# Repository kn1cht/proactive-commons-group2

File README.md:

# proactive-commons-group2
proactive-commons-group2 project

## Shiftr.io with ESP32
Please refer to [ESP32 + Noodl + MQTTでpub/subを試してみる - Qiita](https://qiita.com/masaya-oguro/items/5def128399bde690d8a7#%E4%BD%BF%E3%81%84%E6%96%B9).

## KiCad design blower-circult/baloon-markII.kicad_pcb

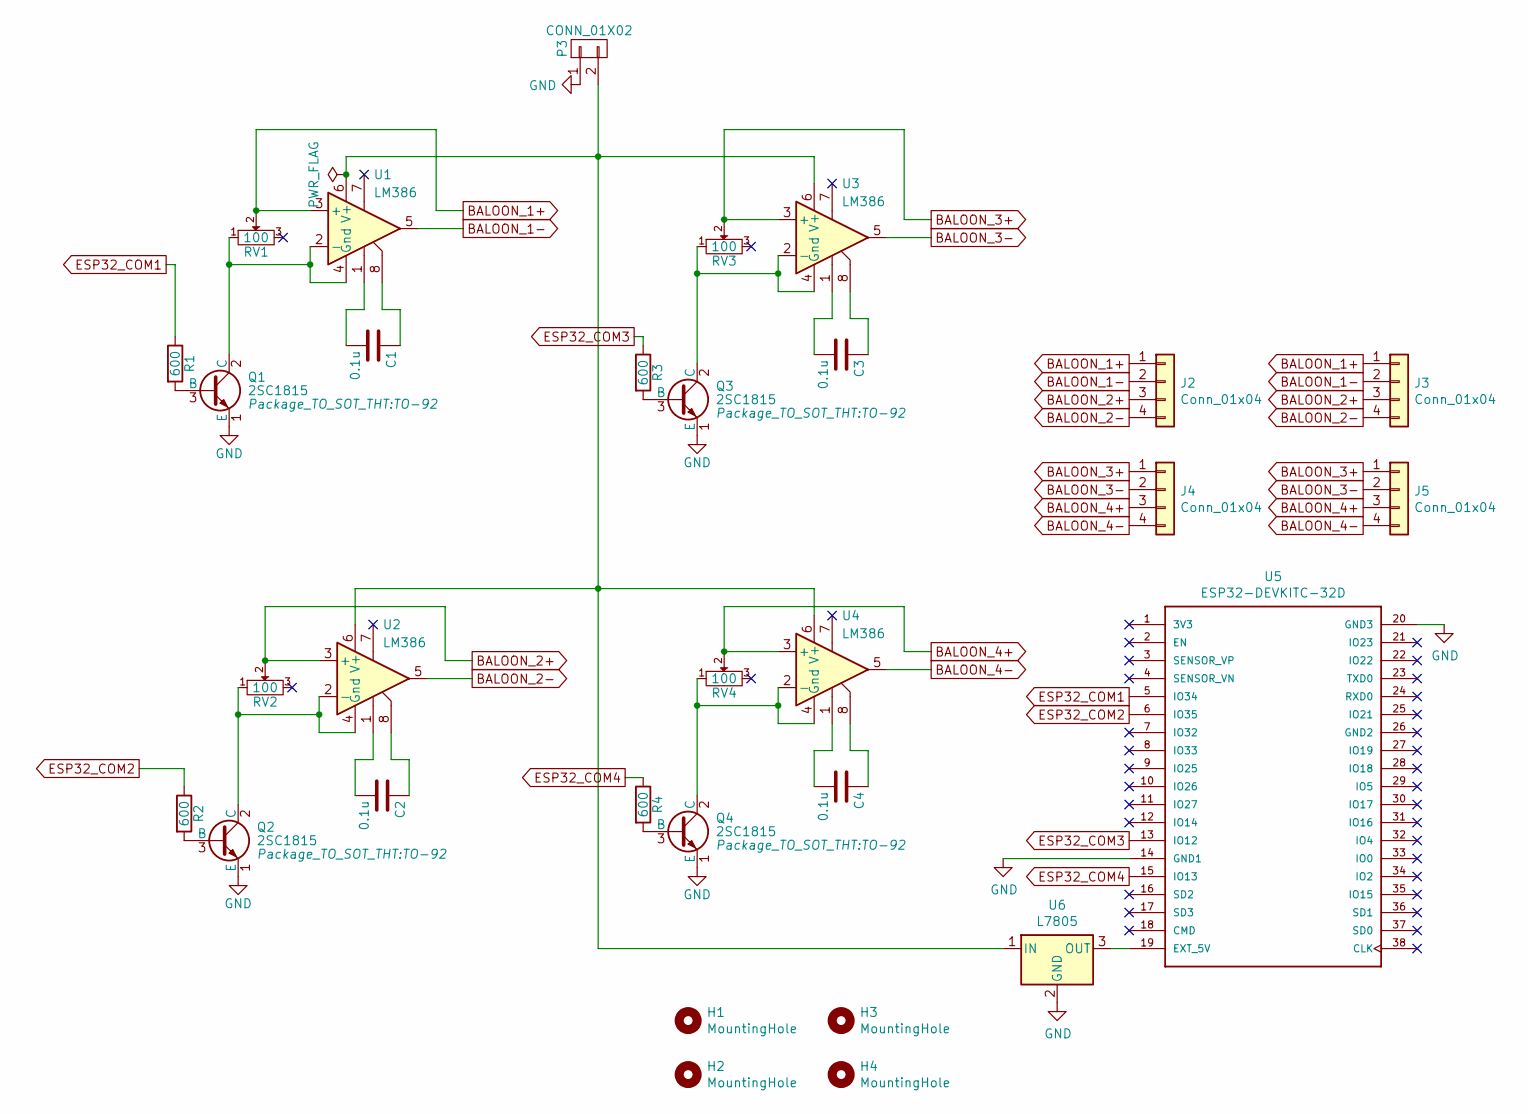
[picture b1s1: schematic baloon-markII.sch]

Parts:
C1, C2, C3, C4: 0.1u; C_Disc_D6.0mm_W2.5mm_P5.00mm
H1, H2, H3, H4: MountingHole; MountingHole_3.2mm_M3
J2, J3, J4, J5: Conn_01x04; Molex_SPOX_5267-04A_1x04_P2.50mm_Vertical
P3: CONN_01X02; Molex_SPOX_5267-02A_1x02_P2.50mm_Vertical
Q1, Q2, Q3, Q4: 2SC1815; TO-92
R1, R2, R3, R4: 600; R_Axial_DIN0204_L3.6mm_D1.6mm_P7.62mm_Horizontal
RV1, RV2, RV3, RV4: 100; Potentiometer_ACP_CA9-H5_Horizontal
U1, U2, U3, U4: LM386; DIP-8_W7.62mm_Socket
U5: ESP32-DEVKITC-32D; MODULE_ESP32-DEVKITC-32D
U6: L7805; TO-220F-3_Horizontal_TabDown

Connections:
BALOON_1+: J2.1, J3.1, RV1.2, U1.3 (+)
BALOON_1-: J2.2, J3.2, U1.5
BALOON_2+: J2.3, J3.3, RV2.2, U2.3 (+)
BALOON_2-: J2.4, J3.4, U2.5
BALOON_3+: J4.1, J5.1, RV3.2, U3.3 (+)
BALOON_3-: J4.2, J5.2, U3.5
BALOON_4+: J4.3, J5.3, RV4.2, U4.3 (+)
BALOON_4-: J4.4, J5.4, U4.5
ESP32_COM1: R1.1, U5.5 (IO34)
ESP32_COM2: R2.1, U5.6 (IO35)
ESP32_COM3: R3.1, U5.13 (IO12)
ESP32_COM4: R4.1, U5.15 (IO13)
GND: P3.1, Q1.1 (E), Q2.1 (E), Q3.1 (E), Q4.1 (E), U5.14 (GND1), U5.20 (GND3), U6.2 (GND)
unnamed: C1.1, U1.8
unnamed: C1.2, U1.1
unnamed: C2.1, U2.8
unnamed: C2.2, U2.1
unnamed: C3.1, U3.8
unnamed: C3.2, U3.1
unnamed: C4.1, U4.8
unnamed: C4.2, U4.1
unnamed: P3.2, U1.6 (V+), U2.6 (V+), U3.6 (V+), U4.6 (V+), U6.1 (IN)
unnamed: Q1.2 (C), RV1.1, U1.2 (-), U1.4 (Gnd)
unnamed: Q1.3 (B), R1.2
unnamed: Q2.2 (C), RV2.1, U2.2 (-), U2.4 (Gnd)
unnamed: Q2.3 (B), R2.2
unnamed: Q3.2 (C), RV3.1, U3.2 (-), U3.4 (Gnd)
unnamed: Q3.3 (B), R3.2
unnamed: Q4.2 (C), RV4.1, U4.2 (-), U4.4 (Gnd)
unnamed: Q4.3 (B), R4.2
unnamed: U5.19 (EXT_5V), U6.3 (OUT)

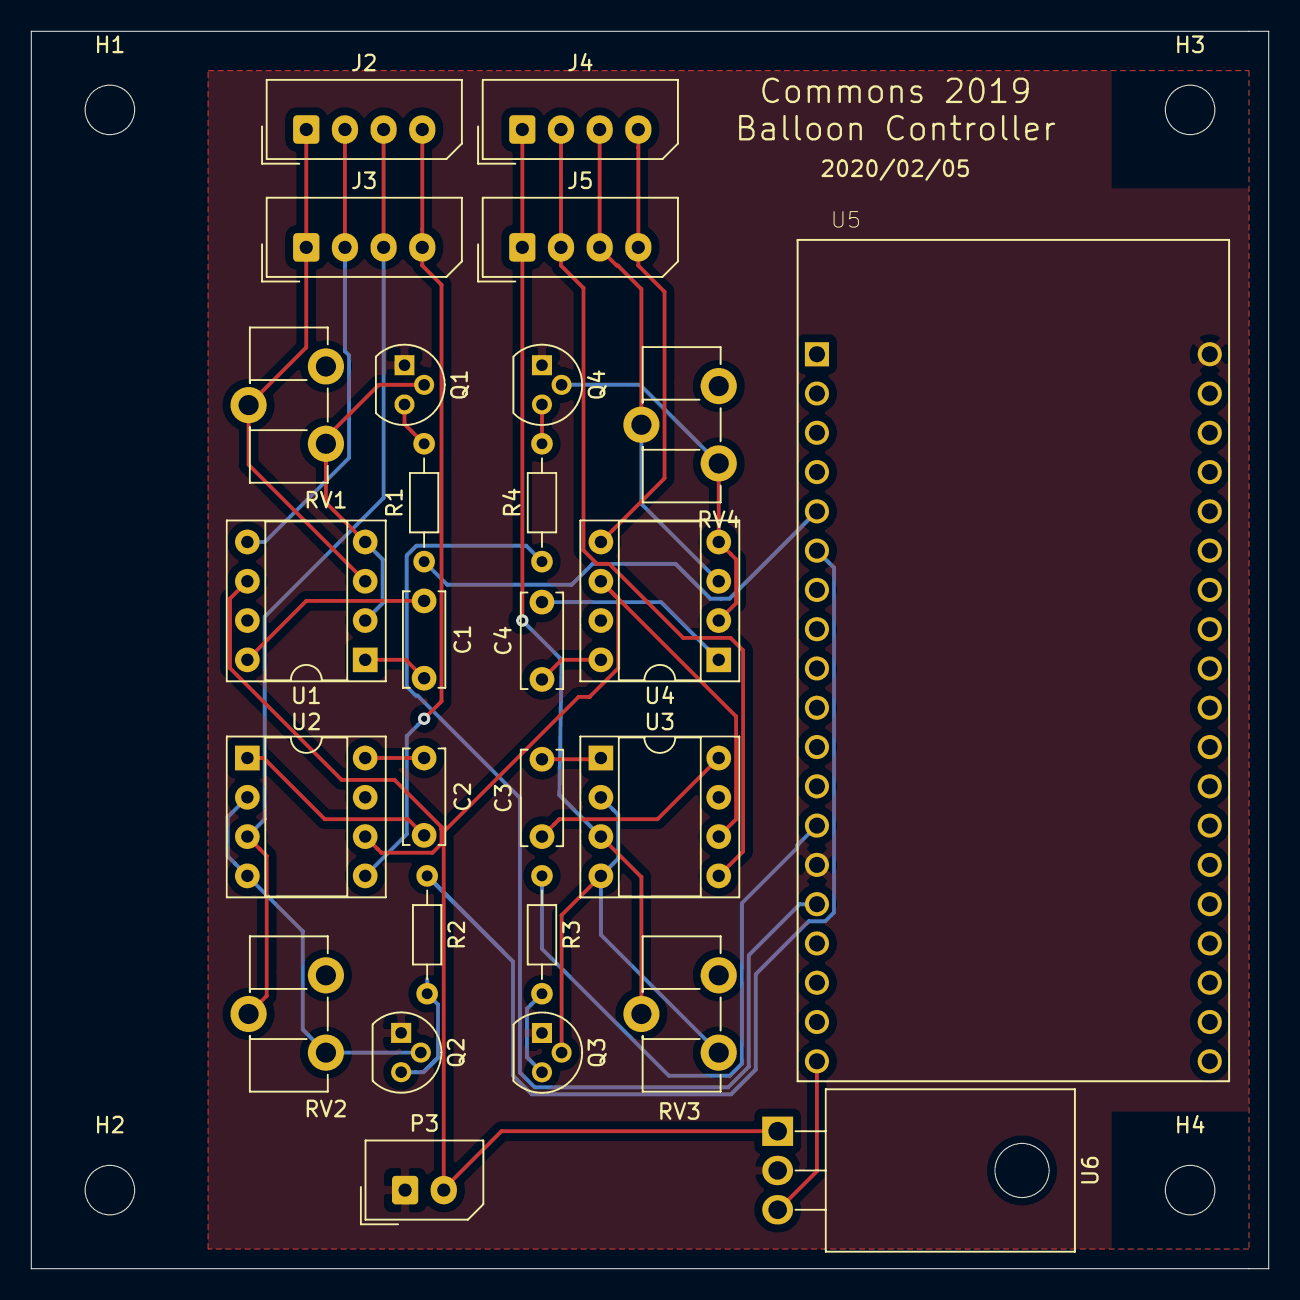
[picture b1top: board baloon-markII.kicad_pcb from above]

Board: 2 copper layers, 80.0 x 80.0 mm, 31 parts (0 on the bottom side), 31 nets.

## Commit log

2019-09-29 add blower_balloon
2019-09-29 add mqtt examples
2019-09-29 implement blower balloon
2019-09-29 add Noodl project
2019-09-29 command to pin output
2019-09-30 embed shiftr into Noodl
2019-09-30 fix README
2019-09-30 add gyouretsu_sensor
2019-10-01 fix sensor logic
2019-10-02 add string status
2019-10-02 fix UI for demo
2019-10-03 add sensor viewer
2019-10-04 small fix
2020-02-06 add circult
2020-02-13 add partslist
2020-02-17 tmmf2020
